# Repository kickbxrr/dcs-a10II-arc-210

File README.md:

# DCS ARC-210 Radio head

I got this faceplate from **SFSauto** on etsy [A10 ARC210](https://www.etsy.com/listing/1082384231/a10-thunderbolt-left-console-vhf-uhf),
but it seem like either this guy makes them for PC flights.com or got them from them. They are also available
from [PC flights.com](https://pcflights.com), direct link [a-10c-thunderbolt-warthog-vhf-uhf-panel](https://pcflights.com/a-10c-thunderbolt-warthog-vhf-uhf-panel/)

# Summary
This project is a flight sim ARC-210 style radio panel for use with DCS.
The first target interface is USB HID joystick/game-controller input from a Raspberry Pi Pico.

The panel needs to support:
- 14 push buttons
- 7 rotary encoders, without integrated push buttons
- 2 single-pole 8-position rotary switches with 45 degree throw; 7 usable positions each and the eighth mechanically locked out
- Optional SPI display later

# Main design decision
Use the Raspberry Pi Pico for timing-sensitive and analog inputs, and use an I2C I/O expander for the simple push buttons.

There are too many inputs for a clean direct-to-GPIO design on a Raspberry Pi Pico.

Raw direct input count:

- 14 push buttons = 14 digital inputs
- 7 rotary encoders = 14 digital inputs
- 2 rotary switches = 14 digital inputs when only 7 positions per switch are enabled

That would require 42 digital inputs before allowing any pins for an SPI display.
The Pico does not have enough spare GPIO for that approach.

Initeial hardware allocation:

- Raspberry Pi Pico direct GPIO:
  - 7 rotary encoders, 2 GPIO per encoder
  - SPI display pins reserved for future use
  - I2C SDA/SCL for the I/O expander
- Raspberry Pi Pico ADC:
  - 8-position rotary switch 1 through an analog resistor ladder
  - 8-position rotary switch 2 through an analog resistor ladder
  - GP28 / ADC2 **spare**
- MCP23017 I2C I/O expander:
  - 14 push buttons
  - 2 spare expanded digital inputs

# Pico pin allocation
The following allocation keeps all seven encoders on direct Pico GPIO,
places the selector ladders on two of the three exposed ADC pins, and
reserves a complete SPI display interface. Pin numbers in parentheses are
Raspberry Pi Pico physical header pins.

| Function | Pico GPIO | Header pins | Wiring notes |
| --- | --- | --- | --- |
| Encoder 1 | GP0, GP1 | 1, 2 | A, B; encoder common to GND |
| Encoder 2 | GP2, GP3 | 4, 5 | A, B; encoder common to GND |
| MCP23017 I2C | GP4, GP5 | 6, 7 | SDA, SCL; I2C0 at 400kHz |
| Encoder 3 | GP6, GP7 | 9, 10 | A, B; encoder common to GND |
| Encoder 4 | GP8, GP9 | 11, 12 | A, B; encoder common to GND |
| Encoder 5 | GP10, GP11 | 14, 15 | A, B; encoder common to GND |
| Encoder 6 | GP12, GP13 | 16, 17 | A, B; encoder common to GND |
| Encoder 7 | GP14, GP15 | 19, 20 | A, B; encoder common to GND |
| SPI display MISO, CS | GP16, GP17 | 21, 22 | Reserve MISO only if the chosen display supports reads |
| SPI display SCK, MOSI | GP18, GP19 | 24, 25 | SPI0 clock and data output |
| SPI display DC, RST, backlight | GP20, GP21, GP22 | 26, 27, 29 | Backlight pin supports PWM dimming |
| Selector 1 ladder | GP26 / ADC0 | 31 | Switch 1 common/wiper through 1K |
| Selector 2 ladder | GP27 / ADC1 | 32 | Switch 2 common/wiper through 1K |
| Spare GPIO / ADC | GP28 / ADC2 | 34 | Available for future analog or digital input; may be used for an MCP interrupt line |

Power and ground allocation:

- Pico pin 36 `3V3(OUT)` powers the MCP23017 and both resistor ladders.
- Use accessible Pico GND pins for the common ground circuit. Encoder commons, button returns, the MCP23017,
- Pin 33 (`AGND`) is used only for both Resistor ladders.
- Do not put 5V on any Pico GPIO, ADC, MCP23017 logic, or resistor-ladder connection.

# I/O expander

I used the Waveshare MCP23017 IO Expansion Board I2C. This was a little pricy given the $12 prive per unit.
This is 2x the price of the Pico. There are some alternatives and if you go to a DIP you can find them for
$1.67 as of writing this doc. Using those will be a bit more work. There are also plenty of cheap alternatives
on Amazon, E-bay, Ali-express etc...

I'm using the MCP23017 for push buttons only. Rotary encoders should stay on Pico GPIO because they are timing-sensitive.

The MCP23017 adds 16 digital I/O pins while using only 2 Pico pins for I2C. The Pico remains in
charge: it asks the MCP23017 for its input state over I2C, and the MCP23017 returns a 16-bit value
where each bit represents one expander pin.

How I wired it to the Raspberry Pi Pico:
```text
Pico 3V3  -> MCP23017 VCC
Pico GND  -> MCP23017 GND
Pico SDA  -> MCP23017 SDA
Pico SCL  -> MCP23017 SCL

Each push button:
MCP23017 input pin -> button -> GND
```

Use `GP4` for SDA and `GP5` for SCL. The Arduino sketch configures this I2C0 bus at 400kHz.
The Waveshare board should provide the required I2C pull-ups; do not add more pull-ups until
the board documentation has been checked.

Configure the MCP23017 inputs with internal pull-ups in firmware. No external pull-up resistors
are required for the 14 buttons. A pressed button should read low.

Button state logic:

```text
button not pressed = input reads HIGH / 1
button pressed     = input connected to GND, reads LOW / 0
```

Suggested button pin mapping be based on the exact MCP23017 chip you use. In my original prototype where I just used wires to connect everyting used whatever was convienent

For my PCB, I think I used GPB0-7 and GPA0-5.

## Polling versus interrupts

Selected approach: poll the MCP23017 every 5ms and debounce each button in firmware for about 20-30ms.

Polling is the preferred first implementation because it needs no additional Pico GPIO or wiring, is easy to debug, and has more than enough response speed for panel buttons. At a 5ms interval, a press is seen within 5ms before debounce; the I2C traffic and Pico CPU cost are negligible.

The MCP23017 interrupt outputs are useful only if future firmware needs to avoid idle I2C reads, put the Pico to sleep, or manages several expanders. Interrupts add an extra wire and more firmware state: switch bounce can cause repeated interrupts, and the Pico must read the MCP23017 `GPIO` or `INTCAP` register to clear the asserted interrupt.

Do not wire the interrupt output for the first version. A future version can connect mirrored, open-drain `INTA`/`INTB` to spare `GP28`, with a 3.3V pull-up, if interrupt-driven input becomes useful.

Button event flow:

```text
Button press
  -> MCP23017 input pin goes LOW
  -> Pico reads MCP23017 over I2C
  -> Pico sees that bit changed from 1 to 0
  -> Pico debounces the change
  -> Pico sends USB HID joystick button pressed to DCS
```

Run the MCP23017 board at 3.3V with the Pico. Keeping the control wiring at 3.3V avoids level-safety issues because Pico GPIO are not 5V tolerant.

I picked the Waveshare board over a generic MCP23017 module because it is documented, exposes address selection, and exposes interrupt pins. The interrupt pins are optional; simple polling is acceptable for push buttons.

Multiple MCP23017 boards can share the same Pico I2C bus if they have different I2C addresses. The MCP23017 supports address selection with A0/A1/A2, which allows up to 8 MCP23017 devices on the same bus.

# 8-position rotary switches (seven enabled positions)

The two 8-position switches are single-pole 8-position rotary switches.

Known switch specifications:

- Voltage rating: 125V
- Current rating: 2.5A AC, 350mA DC
- Actuator type: flatted, 6.35mm diameter
- Actuator length: 38mm
- Depth behind panel: 14.48mm
- Panel cutout: circular, 9.80mm diameter
- Number of positions: 8
- Angle of throw: 45 degrees

Recommended wiring approach: use each switch as an ADC resistor ladder so each rotary switch consumes
one Pico ADC input instead of seven digital inputs.

The eighth physical switch position is mechanically locked out. The circuit therefore provides
seven valid selector readings. Wire the disabled eighth throw to GND as an invalid diagnostic value,
rather than leaving it floating.

## Resistor ladder concept

The Pico ADC reads voltage. A resistor ladder creates a set of known voltages between 3.3V and GND. The rotary switch selects one of those voltage taps and sends it to the ADC input.

Use one resistor ladder per switch. The two switches cannot share a ladder because each common/wiper needs an independent ADC voltage at the same time.

Resistor ladder:
```text
3V3
 |
[10k]
 |---- switch throw 7  ~2.89V
[10k]
 |---- switch throw 6  ~2.48V
[10k]
 |---- switch throw 5  ~2.06V
[10k]
 |---- switch throw 4  ~1.65V
[10k]
 |---- switch throw 3  ~1.24V
[10k]
 |---- switch throw 2  ~0.83V
[10k]
 |---- switch throw 1  ~0.41V
[10k]
 |
GND
```

The switch common/wiper is the output:

```text
Switch common/wiper -> 1k resistor -> Pico ADC input
Pico ADC input -> 100nF capacitor -> GND
```

The 1k resistor protects the ADC input from brief wiring or contact transients. The 100nF capacitor smooths noise and contact chatter, and provides a low-impedance source while the Pico ADC samples. A pulldown is not required. Do not use a 100k pulldown: it would load the ladder and shift the expected voltages. A 1M pulldown is optional only if it is bought separately.

## Recommended parts

For each rotary switch:

- 8x 10k ohm resistors, for the ladder
- Small perfboard or stripboard
- 24-26 AWG hookup wire
- *Optional* 3-pin connector for 3V3, GND, and ADC signal

Use the available 10k resistors for the ladder in series with the ADC. With 8 x 10k resistors,
the ladder is 80k total and draws about 41uA from 3.3V. The voltage steps are wide enough for
reliable detection while keeping current draw low.

## Assembly steps
1. Use a multimeter to identify the switch common/wiper pin.
2. Build the 8-resistor chain on a small perfboard.
3. Connect the top of the chain to Pico 3V3.
4. Connect the bottom of the chain to the common ground circuit that returns to Pico physical pin 23.
5. Run one wire from each of the seven ladder taps to the corresponding active switch throw terminal.
6. Run the switch common/wiper through a 1k resistor to the Pico ADC pin.
7. Put a 100nF capacitor from the ADC pin side of the 1k resistor to GND.
8. Wire the locked-out eighth switch terminal directly to GND so it decodes as an invalid position if it is ever reached.
9. In firmware, read the ADC and map voltage ranges to positions 1-7.

**Suggested** Pico ADC allocation:

```text
Switch 1 common/wiper -> Pico GP26 / ADC0
Switch 2 common/wiper -> Pico GP27 / ADC1
Spare                  -> Pico GP28 / ADC2
```

## Expected ADC values
For a 12-bit ADC reading from 0-4095, approximate values are:

```text
Position 1:  512
Position 2: 1024
Position 3: 1536
Position 4: 2048
Position 5: 2559
Position 6: 3071
Position 7: 3583
Locked-out position: approximately 0 (invalid)
```

Firmware should define threshold ranges for each position instead of checking exact values. A good starting point is to place each threshold halfway between adjacent expected values, then require the decoded position to remain stable for 20-50ms before accepting the change.

## Interface to DCS

Initial recommendation: USB HID joystick/game-controller firmware using Arduino with the Arduino-Pico core.

Benefits:

- Simple host-side setup
- DCS can bind buttons, encoders, and selector pulses through normal controller bindings
- No DCS-specific protocol required for the first version

DCS-BIOS may be worth considering later if the project needs bidirectional state, display synchronization, 
or aircraft-specific radio data. this will be necvessary when the SPI display is added.

# Firmware stack

Selected stack: Arduino IDE with the Arduino-Pico core.

This is the final firmware environment because the project is a USB HID game-controller device. Arduino-Pico provides
a familiar sketch workflow while retaining C++ performance and offering built-in 
USB joystick, keyboard, and mouse support. It is a practical fit on both Windows 11 and macOS. Also I am more familar with 
the C++ environment of Arduino than Python or CMake.

Suggested implementation order:

1. Bring up the Pico in Arduino IDE with the Arduino-Pico board package.
2. Scan the I2C bus and confirm the MCP23017 address, expected to be `0x27` unless its address jumpers are changed. this got me at first since the AI wanted it to be `0x20` and I had to do a lot of looking up the datasheet to find the right address.
3. Configure the 14 MCP23017 pins as `INPUT_PULLUP`; poll both ports every 5ms and debounce button state changes for 20-30ms.
4. Read the two selector ADC inputs; decode selector positions by threshold range and require a stable reading for 20-50ms.
5. Read the seven encoders directly from Pico GPIO.
6. Send button, selector, and encoder events through USB HID to DCS.

Why Arduino-Pico instead of the Pico SDK:

- Arduino-Pico is C++ with a straightforward sketch, library, compile, and upload workflow. It is easier to iterate on than a standalone CMake project.
- It already provides the USB HID joystick/game-controller capability this panel needs.
- The Pico SDK provides the most control over low-level timing and custom USB descriptors, but its toolchain and CMake project setup are more involved. It remains a good future option if this panel eventually needs a custom HID report beyond what Arduino-Pico provides.

Windows 11 and macOS are both suitable for Arduino-Pico. The finished Pico appears to the computer as a standard USB HID device, so DCS does not need a special driver.

## Initial controller sketch
The initial Arduino sketch is [arc210_controller.ino](./arc210_controller/arc210_controller.ino).

Arduino IDE setup:

1. Install the Arduino-Pico board package and select `Raspberry Pi Pico`.
2. Set `Tools -> USB Stack -> Pico SDK`; the Arduino-Pico `Joystick` library is provided by this USB stack.
3. Install `Adafruit MCP23X17` from Library Manager. Its dependencies, including Adafruit BusIO, should install automatically.
4. Upload the sketch with the Pico connected by USB.

The sketch presents one USB joystick with all 32 buttons used and no analog control assigned:

| HID controls | Source |
| --- | --- |
| Buttons 1-14 | MCP23017 push buttons |
| Buttons 15-26 | Encoder 1-6 positive and negative turns |
| Buttons 27-28 | Encoder 7 positive and negative turns |
| Buttons 29-30 | Selector 1 next and previous position pulses |
| Buttons 31-32 | Selector 2 next and previous position pulses |

The Arduino-Pico joystick descriptor supports 32 buttons, so this allocation uses its entire button capacity. The selectors intentionally emit relative next/previous pulses instead of using fourteen more held buttons, keeping the design within that limit. Bind each selector's next/previous buttons to the matching DCS increment/decrement commands. On startup, align the simulator state with the physical selector positions manually.

## Open items before final schematic

- SPI display model and pin requirements
- Find suitable display

## Initial Prototype
The initial prototype was done on perf boards. I found ut the hard way that drilling and cutting perfboards can have 
some consequences.The worse was getting a few fiberglass splinters. The Pico was mounted on 2 1x20 sockets 
(Technically it was 4 1x10 connectors that I sanded to fit and work like 2 1x20 connectors), and the MCP23017 
was mounted on 2 1x10 connectors.The components are just soldiered together using random wires. the whole thing 
is kind of a mess. It works but it is ugly.

# Phase 2 PCB
I figured it would be cool to see if I can create a PCB.
Watching some youtube videos from the Warthog project and
some DCS community videos of people build button boxes and
different panels made me think I could clean this up a lot.

# Schematic

## PCB Rev B work

The first PCB revision is a panel-sized button carrier. The 14 tactile
buttons mount directly to the PCB; the seven encoders and two selectors
remain faceplate-mounted and connect through cutouts in the PCB. Maybe if
I try to do another prototype I will try surface mounting the compnenets
and try to get an assempled board with all the part already on the board. 
this feel like a big leap from I was hand ouldering crap from perfboards with
a rats nest of wires 3 weeks ago to producing a full PCBA board

Rev B uses a removable Raspberry Pi Pico in two 1x20 sockets,
a socketed MCP23017-E/SP DIP-28 IC, and provisional 6x6mm
tactile-switch footprints. It was ready for fabrication pretty quick.
I', pretty sure my trace routing needs some help, but all the button work
as expected so that is a win in my book.

## Kicad

### 3D Front

### 3d Back

### Actual PCB Front

### Actual PCB Back

## SPI display `Phase 3`
The design reserves pins for a SPI display. A typical SPI display may need:

- SCK
- MOSI
- CS
- DC
- optional RST
- optional backlight control

Using the MCP23017 for push buttons keeps enough Pico pins available for the display.
Direct-to-GPIO wiring for all buttons and switch positions would make the SPI display
difficult to add if impossible.

For the display I get a 3.5" TFT display from Amazon. I did some surgery to remove the display
from the controller board. I figured I would destroy one of the two boards but in a stroke of luck
I got it sorted out on the 1st try.

# How did it all turn out?
TBD!!!

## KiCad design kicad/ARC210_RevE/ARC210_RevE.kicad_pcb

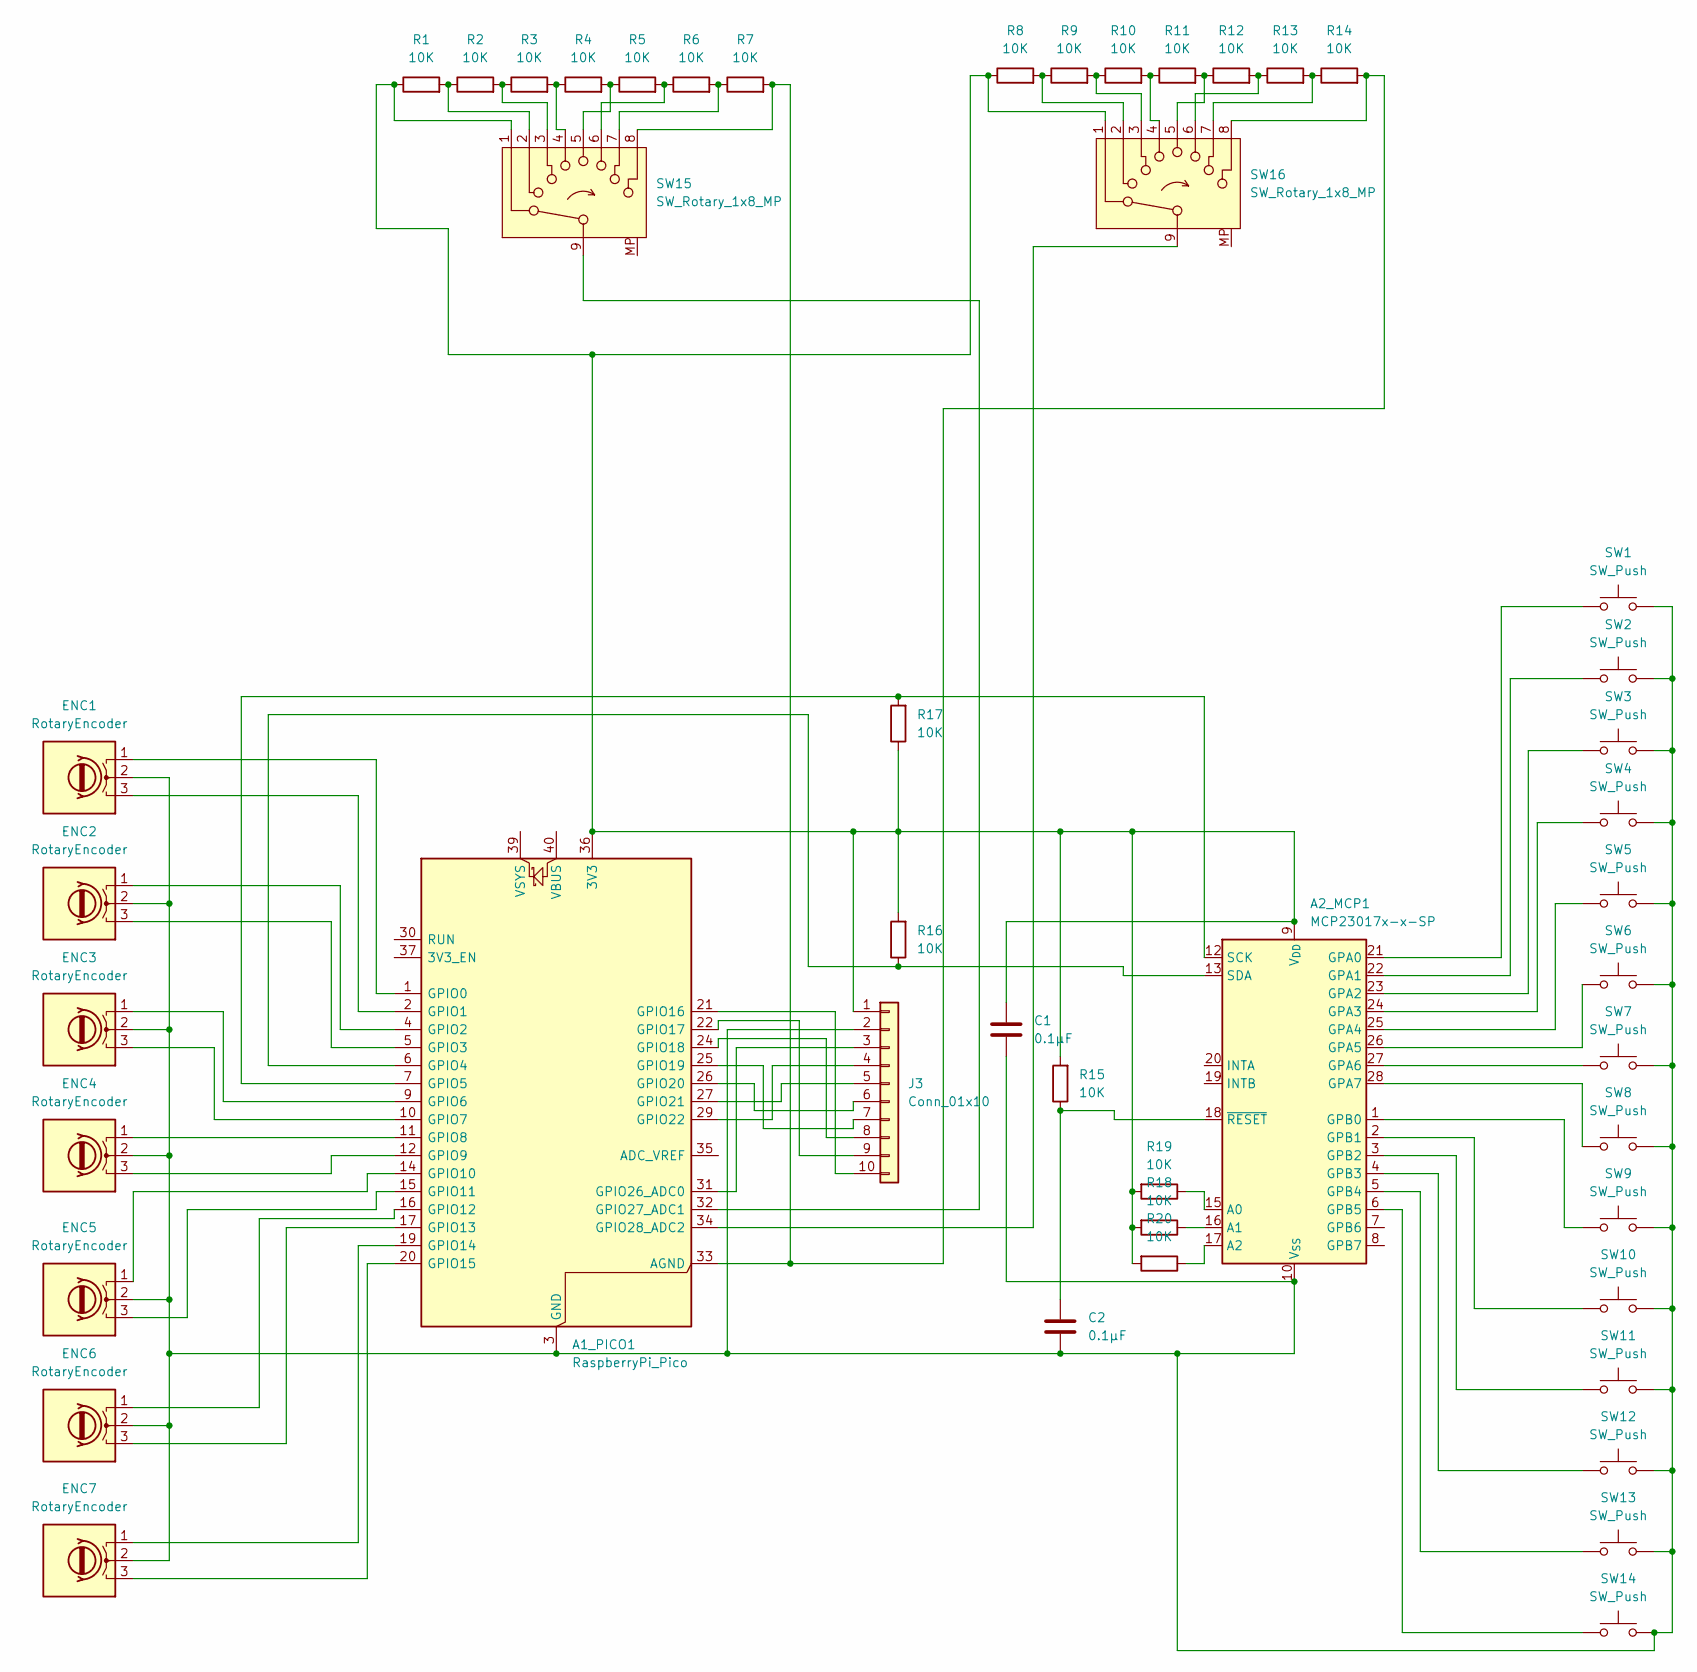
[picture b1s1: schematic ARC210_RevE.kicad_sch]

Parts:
A1_PICO1: RaspberryPi_Pico; RaspberryPi_Pico_Common_SMD
A2_MCP1: MCP23017x-x-SP; SOIC-28W_7.5x17.9mm_P1.27mm
C1, C2: 0.1µF; C_0805_2012Metric_Pad1.18x1.45mm_HandSolder
ENC1, ENC2, ENC3, ENC4, ENC5, ENC6, ENC7: RotaryEncoder; RotaryEncoder_Generic_EC11_Switch_Vertical
J3: Conn_01x10; ER_CON40HT_1x40-1MP_P0.50mm_Horizontal_TopContact
R1, R2, R3, R4, R5, R6, R7, R8, R9, R10, R11, R12, R13, R14: 10K; R_1206_3216Metric_Pad1.30x1.75mm_HandSolder
R15, R16, R17, R18, R19, R20: 10K; R_0805_2012Metric_Pad1.20x1.40mm_HandSolder
SW1, SW2, SW3, SW4, SW5, SW6, SW7, SW8, SW9, SW10, SW11, SW12, SW13, SW14: SW_Push; SW_PUSH_6mm
SW15, SW16: SW_Rotary_1x8_MP; RotarySwitch_P-H397_1P8T

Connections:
unnamed: A1_PICO1.36 (3V3), A2_MCP1.9 (V_{DD}), C1.1, J3.1, R1.1, R8.1, R15.2, R16.2, R17.1, R18.2, R19.2, R20.2, SW15.1, SW16.1
unnamed: A1_PICO1.33 (AGND), R7.2, R14.2, SW15.8, SW16.8
unnamed: A1_PICO1.1 (GPIO0), ENC1.1 (CLK)
unnamed: A1_PICO1.2 (GPIO1), ENC1.3 (DATA)
unnamed: A1_PICO1.4 (GPIO2), ENC2.1 (CLK)
unnamed: A1_PICO1.5 (GPIO3), ENC2.3 (DATA)
unnamed: A1_PICO1.6 (GPIO4), A2_MCP1.13 (SDA), R16.1
unnamed: A1_PICO1.7 (GPIO5), A2_MCP1.12 (SCK), R17.2
unnamed: A1_PICO1.9 (GPIO6), ENC3.1 (CLK)
unnamed: A1_PICO1.10 (GPIO7), ENC3.3 (DATA)
unnamed: A1_PICO1.11 (GPIO8), ENC4.1 (CLK)
unnamed: A1_PICO1.12 (GPIO9), ENC4.3 (DATA)
unnamed: A1_PICO1.14 (GPIO10), ENC5.1 (CLK)
unnamed: A1_PICO1.15 (GPIO11), ENC5.3 (DATA)
unnamed: A1_PICO1.16 (GPIO12), ENC6.1 (CLK)
unnamed: A1_PICO1.17 (GPIO13), ENC6.3 (DATA)
unnamed: A1_PICO1.19 (GPIO14), ENC7.1 (CLK)
unnamed: A1_PICO1.20 (GPIO15), ENC7.3 (DATA)
unnamed: A1_PICO1.21 (GPIO16), J3.10 (pin_10)
unnamed: A1_PICO1.22 (GPIO17), J3.9
unnamed: A1_PICO1.24 (GPIO18), J3.8
unnamed: A1_PICO1.25 (GPIO19), J3.7
unnamed: A1_PICO1.26 (GPIO20), J3.6
unnamed: A1_PICO1.27 (GPIO21), J3.5
unnamed: A1_PICO1.29 (GPIO22), J3.4
unnamed: A1_PICO1.31 (GPIO26_ADC0), J3.3 (pin_3)
unnamed: A1_PICO1.32 (GPIO27_ADC1), SW15.9
unnamed: A1_PICO1.34 (GPIO28_ADC2), SW16.9
unnamed: A2_MCP1.15 (A0), R19.1
unnamed: A2_MCP1.16 (A1), R18.1
unnamed: A2_MCP1.17 (A2), R20.1
unnamed: A2_MCP1.21 (GPA0), SW1.1
unnamed: A2_MCP1.22 (GPA1), SW2.1
unnamed: A2_MCP1.23 (GPA2), SW3.1
unnamed: A2_MCP1.24 (GPA3), SW4.1
unnamed: A2_MCP1.25 (GPA4), SW5.1
unnamed: A2_MCP1.26 (GPA5), SW6.1
unnamed: A2_MCP1.27 (GPA6), SW7.1
unnamed: A2_MCP1.28 (GPA7), SW8.1
unnamed: A2_MCP1.1 (GPB0), SW9.1
unnamed: A2_MCP1.2 (GPB1), SW10.1
unnamed: A2_MCP1.3 (GPB2), SW11.1
unnamed: A2_MCP1.4 (GPB3), SW12.1
unnamed: A2_MCP1.5 (GPB4), SW13.1
unnamed: A2_MCP1.6 (GPB5), SW14.1
unnamed: A1_PICO1.3 (GND), A1_PICO1.8 (GND), A1_PICO1.13 (GND), A1_PICO1.18 (GND), A1_PICO1.23 (GND), A1_PICO1.28 (GND), A1_PICO1.38 (GND), A2_MCP1.10 (V_{SS}), C1.2, C2.2, ENC1.2 (GND), ENC2.2 (GND), ENC3.2 (GND), ENC4.2 (GND), ENC5.2 (GND), ENC6.2 (GND), ENC7.2 (GND), J3.2, SW1.2, SW2.2, SW3.2, SW4.2, SW5.2, SW6.2, SW7.2, SW8.2, SW9.2, SW10.2, SW11.2, SW12.2, SW13.2, SW14.2
unnamed: A2_MCP1.18 (~RESET), C2.1, R15.1
unnamed: R1.2, R2.1, SW15.2
unnamed: R2.2, R3.1, SW15.3
unnamed: R3.2, R4.1, SW15.4
unnamed: R4.2, R5.1, SW15.5
unnamed: R5.2, R6.1, SW15.6
unnamed: R6.2, R7.1, SW15.7
unnamed: R8.2, R9.1, SW16.2
unnamed: R9.2, R10.1, SW16.3
unnamed: R10.2, R11.1, SW16.4
unnamed: R11.2, R12.1, SW16.5
unnamed: R12.2, R13.1, SW16.6
unnamed: R13.2, R14.1, SW16.7

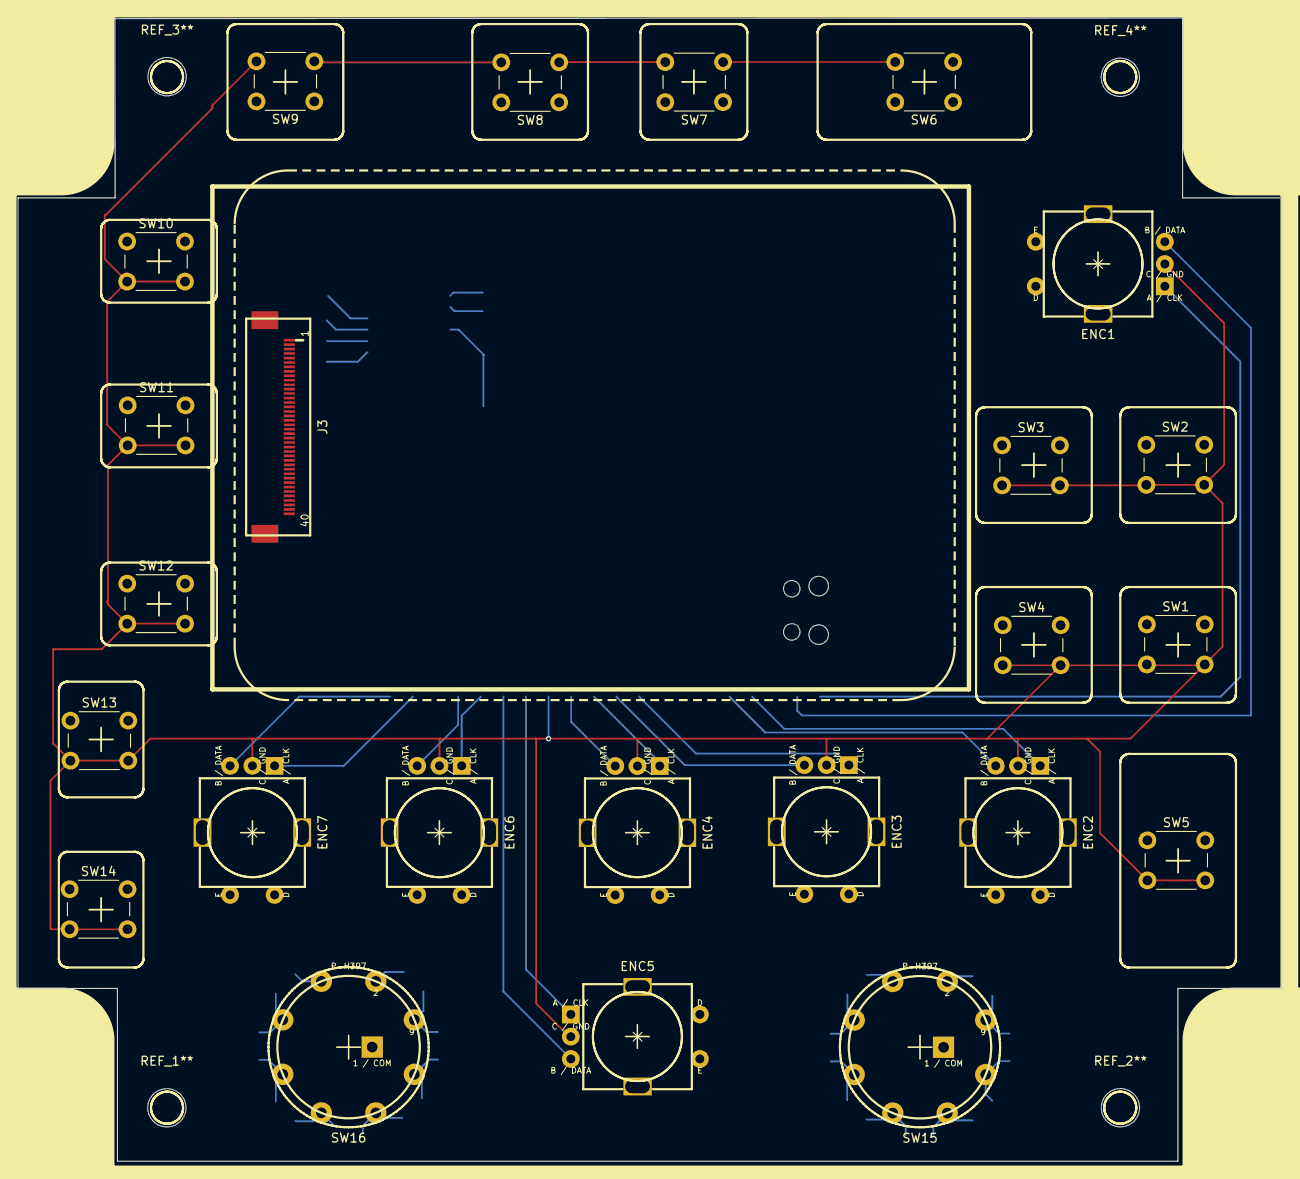
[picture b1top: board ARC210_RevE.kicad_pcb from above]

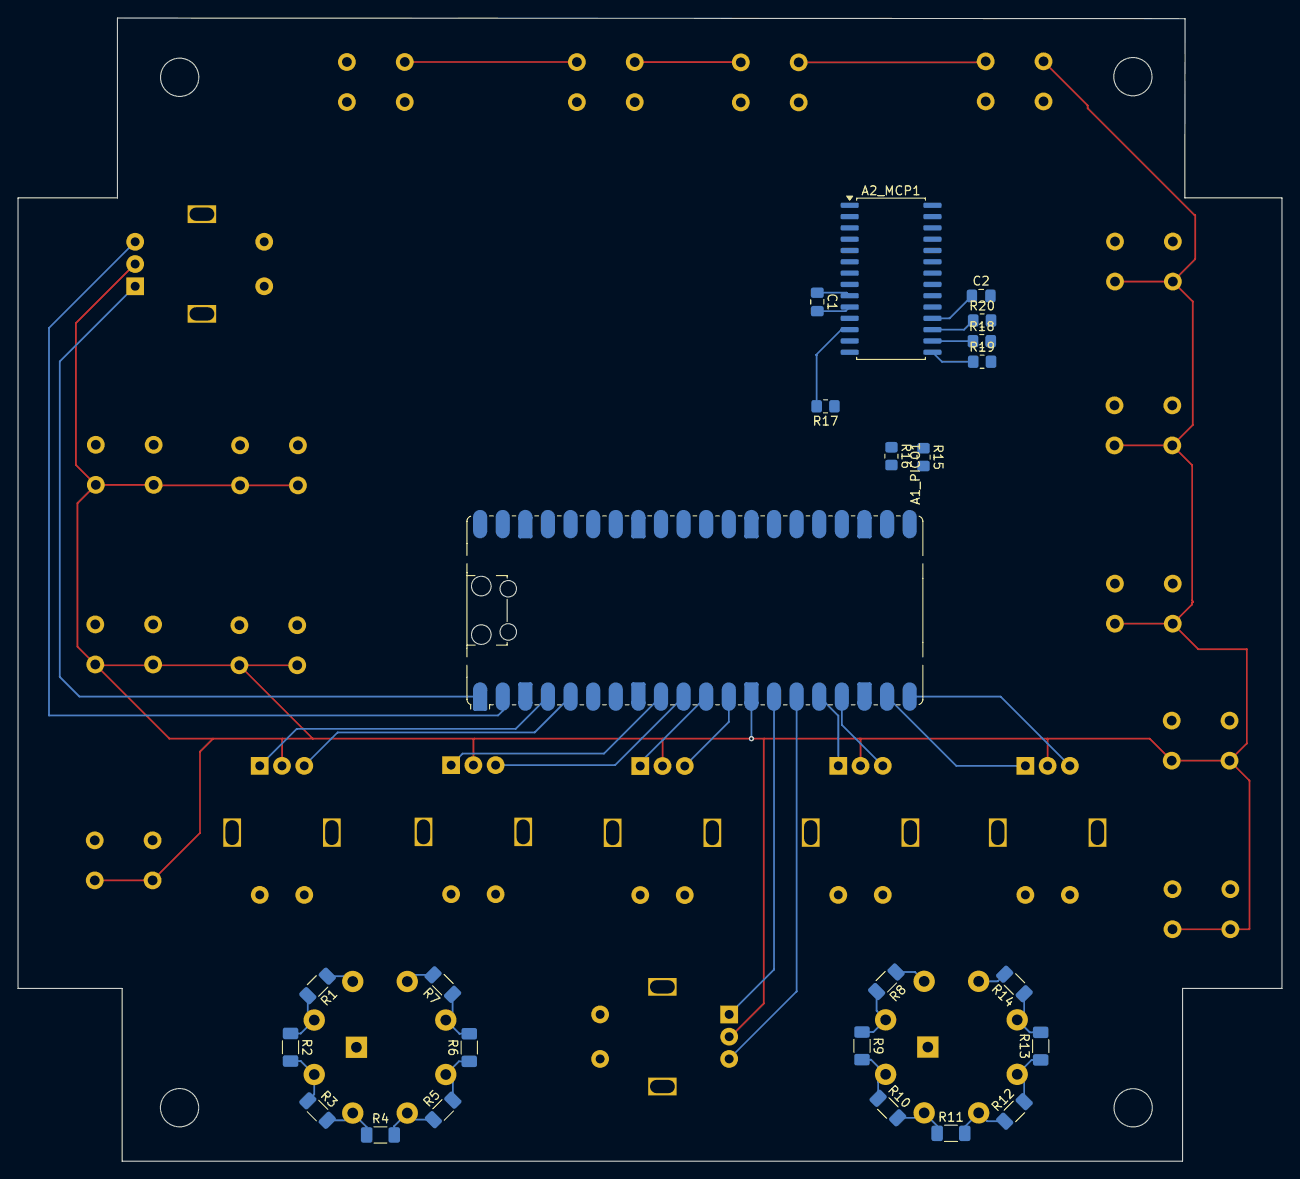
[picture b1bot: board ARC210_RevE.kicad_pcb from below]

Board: 2 copper layers, 142.0 x 128.4 mm, 52 parts (24 on the bottom side), 59 nets.

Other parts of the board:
REF_1**, REF_2**, REF_3**, REF_4**: MountingHole_4.3mm_M4

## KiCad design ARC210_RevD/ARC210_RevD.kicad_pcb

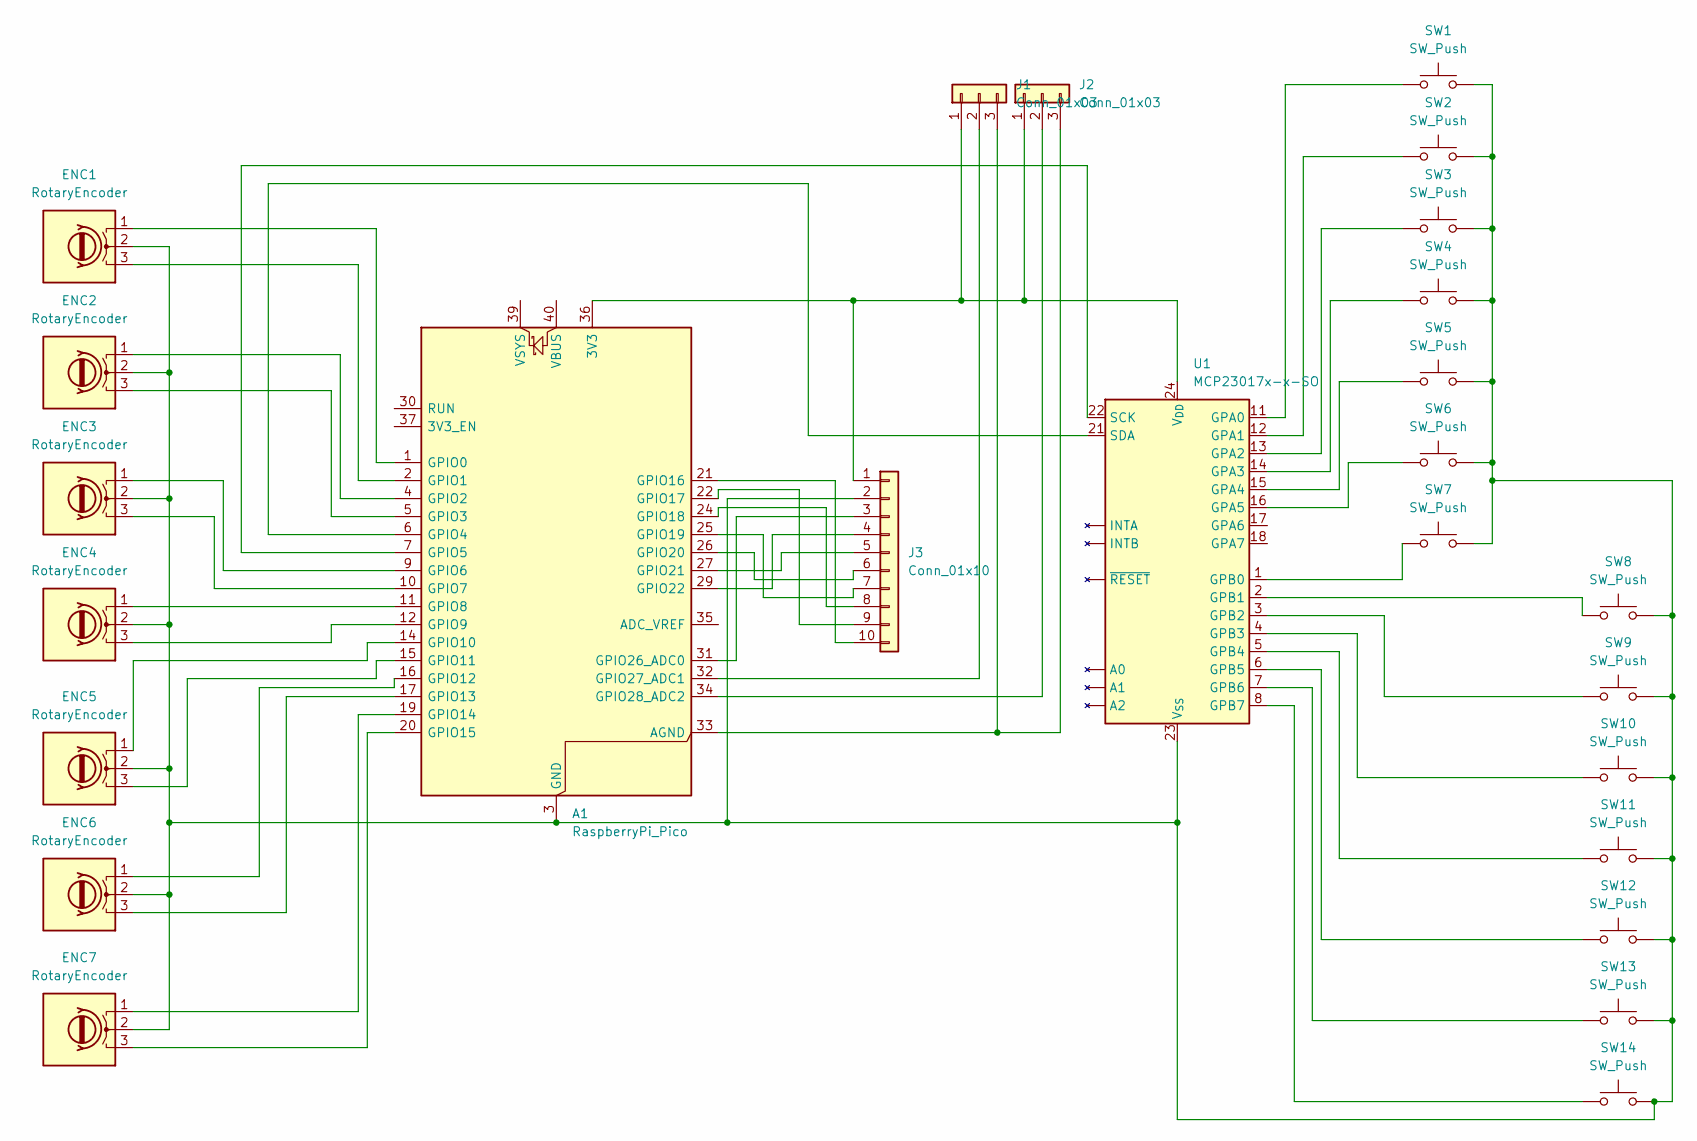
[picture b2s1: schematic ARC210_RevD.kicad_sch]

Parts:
A1: RaspberryPi_Pico; Pico_mount
ENC1, ENC2, ENC3, ENC4, ENC5, ENC6, ENC7: RotaryEncoder; SolderWire-0.5sqmm_1x03_P4.8mm_D0.9mm_OD2.3mm
J1, J2: Conn_01x03; SolderWire-0.5sqmm_1x03_P4.6mm_D0.9mm_OD2.1mm
J3: Conn_01x10; PinHeader_1x10_P2.54mm_Vertical
SW1, SW2, SW3, SW4, SW5, SW6, SW7, SW8, SW9, SW10, SW11, SW12, SW13, SW14: SW_Push; SW_PUSH_6mm
U1: MCP23017x-x-SO; MCP23017_mount

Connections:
unnamed: A1.36 (3V3), J1.1 (3v3), J2.1 (3v3), J3.1, U1.24 (V_{DD})
unnamed: A1.33 (AGND), J1.3 (GND), J2.3 (GND)
unnamed: A1.1 (GPIO0), ENC1.1 (CLK)
unnamed: A1.2 (GPIO1), ENC1.3 (DATA)
unnamed: A1.4 (GPIO2), ENC2.1 (CLK)
unnamed: A1.5 (GPIO3), ENC2.3 (DATA)
unnamed: A1.6 (GPIO4), U1.21 (SDA)
unnamed: A1.7 (GPIO5), U1.22 (SCK)
unnamed: A1.9 (GPIO6), ENC3.1 (CLK)
unnamed: A1.10 (GPIO7), ENC3.3 (DATA)
unnamed: A1.11 (GPIO8), ENC4.1 (CLK)
unnamed: A1.12 (GPIO9), ENC4.3 (DATA)
unnamed: A1.14 (GPIO10), ENC5.1 (CLK)
unnamed: A1.15 (GPIO11), ENC5.3 (DATA)
unnamed: A1.16 (GPIO12), ENC6.1 (CLK)
unnamed: A1.17 (GPIO13), ENC6.3 (DATA)
unnamed: A1.19 (GPIO14), ENC7.1 (CLK)
unnamed: A1.20 (GPIO15), ENC7.3 (DATA)
unnamed: A1.21 (GPIO16), J3.10 (pin_10)
unnamed: A1.22 (GPIO17), J3.9
unnamed: A1.24 (GPIO18), J3.8
unnamed: A1.25 (GPIO19), J3.7
unnamed: A1.26 (GPIO20), J3.6
unnamed: A1.27 (GPIO21), J3.5
unnamed: A1.29 (GPIO22), J3.4
unnamed: A1.31 (GPIO26_ADC0), J3.3 (pin_3)
unnamed: A1.32 (GPIO27_ADC1), J1.2 (ADC)
unnamed: A1.34 (GPIO28_ADC2), J2.2 (ADC)
unnamed: A1.3 (GND), A1.8 (GND), A1.13 (GND), A1.18 (GND), A1.23 (GND), A1.28 (GND), A1.38 (GND), ENC1.2 (GND), ENC2.2 (GND), ENC3.2 (GND), ENC4.2 (GND), ENC5.2 (GND), ENC6.2 (GND), ENC7.2 (GND), J3.2, SW1.2, SW2.2, SW3.2, SW4.2, SW5.2, SW6.2, SW7.2, SW8.2, SW9.2, SW10.2, SW11.2, SW12.2, SW13.2, SW14.2, U1.23 (V_{SS})
unnamed: SW1.1, U1.11 (GPA0)
unnamed: SW2.1, U1.12 (GPA1)
unnamed: SW3.1, U1.13 (GPA2)
unnamed: SW4.1, U1.14 (GPA3)
unnamed: SW5.1, U1.15 (GPA4)
unnamed: SW6.1, U1.16 (GPA5)
unnamed: SW7.1, U1.1 (GPB0)
unnamed: SW8.1, U1.2 (GPB1)
unnamed: SW9.1, U1.3 (GPB2)
unnamed: SW10.1, U1.4 (GPB3)
unnamed: SW11.1, U1.5 (GPB4)
unnamed: SW12.1, U1.6 (GPB5)
unnamed: SW13.1, U1.7 (GPB6)
unnamed: SW14.1, U1.8 (GPB7)

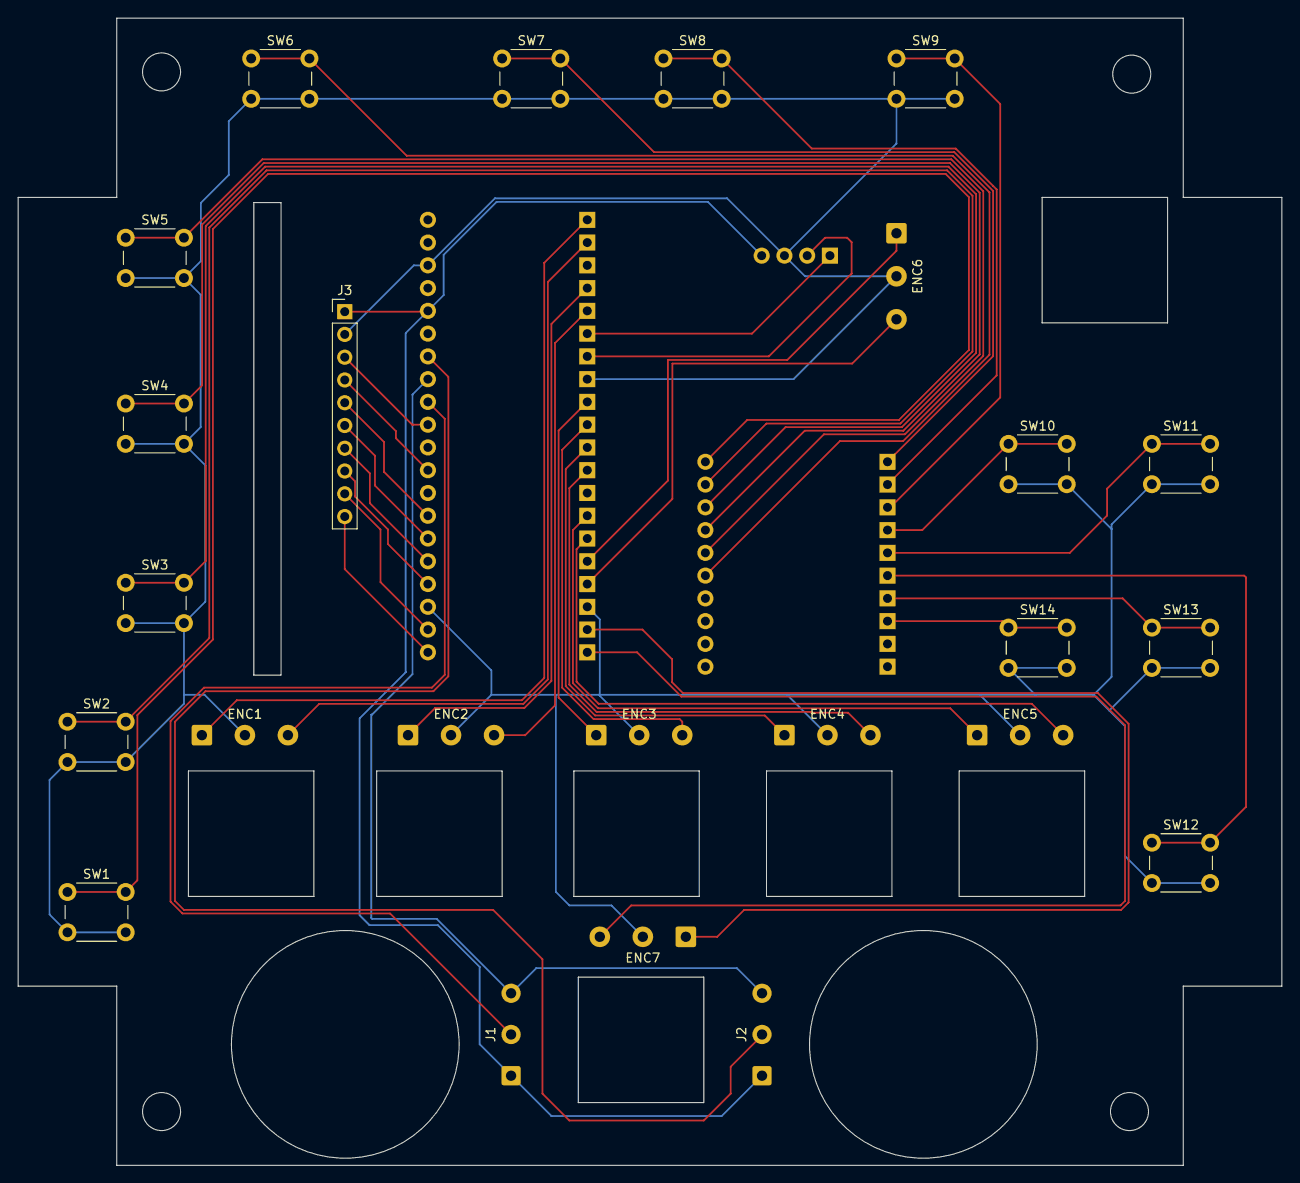
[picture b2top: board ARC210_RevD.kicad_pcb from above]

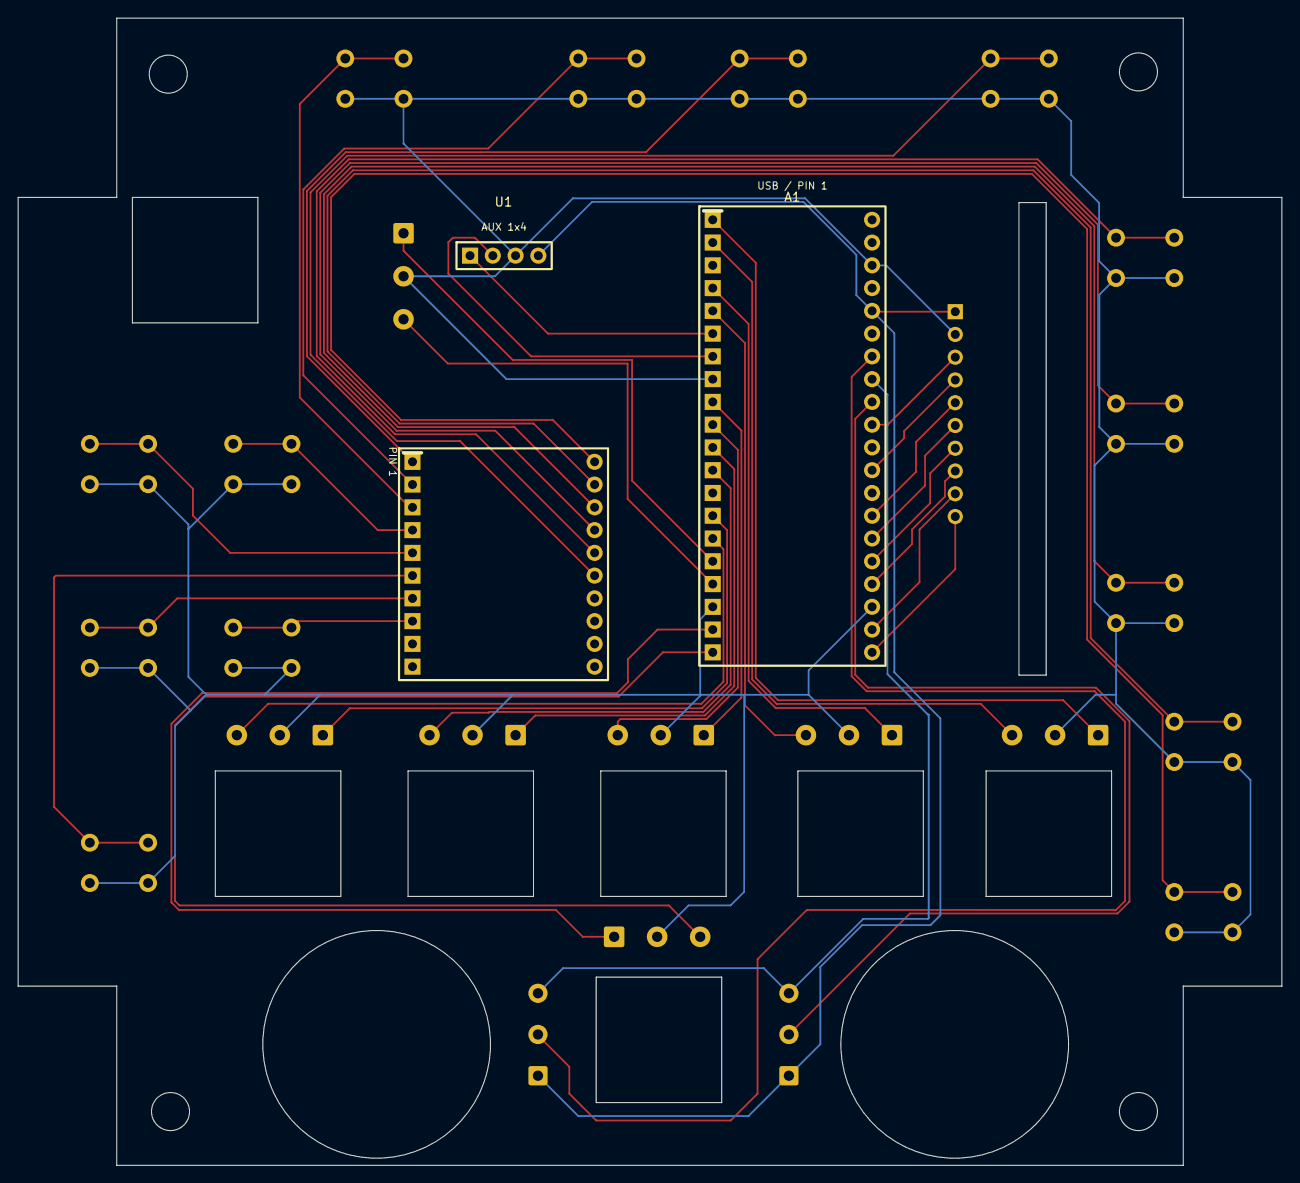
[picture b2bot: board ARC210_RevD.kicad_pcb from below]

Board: 2 copper layers, 141.0 x 128.0 mm, 26 parts (2 on the bottom side), 43 nets.
